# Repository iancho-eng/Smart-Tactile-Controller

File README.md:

# Smart Tactile Controller

A five-key USB-C macro pad built around an ESP32-C3 — from KiCad schematic to fabricated PCB and 3D-printed enclosure.

---

## Overview

The Smart Tactile Controller is a compact 5-key macro pad powered by an **ESP32-C3-MINI-1** module, giving it onboard Wi-Fi and BLE for wireless macro/HID use in addition to wired USB-C. The full design — schematic, PCB layout, and enclosure — was taken from concept to a fabricated, assembled board.

## Key Specifications

| Property         | Value                                              |
| ----------------- | --------------------------------------------------- |
| MCU               | ESP32-C3-MINI-1 (RISC-V, Wi-Fi + BLE)               |
| Power             | USB-C input via AP2112K-3.3 LDO regulator            |
| Input             | 5 × Cherry MX–compatible mechanical switches         |
| PCB               | 2-layer, 58 × 85 mm, 0402/0603 SMD components        |
| Enclosure         | 3D-printed, custom-designed                          |
| Cost              | ~$5 per board (PCBWay)                               |

## Hardware Files

| File                                             | Description                                    |
| -------------------------------------------------- | ------------------------------------------------- |
| [`hardware/Smart_Tactile_Controller.kicad_sch`](hardware/Smart_Tactile_Controller.kicad_sch) | Full schematic (ESP32-C3, LDO regulator, USB-C, switch matrix) |
| [`hardware/Smart_Tactile_Controller.kicad_pcb`](hardware/Smart_Tactile_Controller.kicad_pcb) | Routed 2-layer PCB layout                        |
| [`hardware/Smart_Tactile_Controller_Print.stl`](hardware/Smart_Tactile_Controller_Print.stl) | 3D-printable enclosure                           |

Open the `.kicad_sch` / `.kicad_pcb` files in **KiCad 10** to view or edit the design. The `.stl` can be sliced directly for 3D printing.

## GitHub Pages Deployment

This repo can be hosted as a static project site via GitHub Pages:

1. Push to the `main` branch.
2. In the repo settings, go to **Pages** and set the source to `main` / root (or `/docs` if you move `index.html` there).
3. The site will be published at `https://iancho-eng.github.io/Smart-Tactile-Controller/`.

### Local Preview

To preview the site locally before pushing:

```bash
python3 -m http.server 8000
```

Then open `http://localhost:8000` in your browser.

## License

Consider adding a [CERN-OHL](https://cern-ohl.web.cern.ch/) or MIT license to make the hardware design freely reusable by others.

## Status

- [x] Schematic designed in KiCad
- [x] PCB routed (2-layer)
- [x] Enclosure designed and 3D printed
- [x] Board fabricated and assembled
- [ ] Firmware / HID mapping documented

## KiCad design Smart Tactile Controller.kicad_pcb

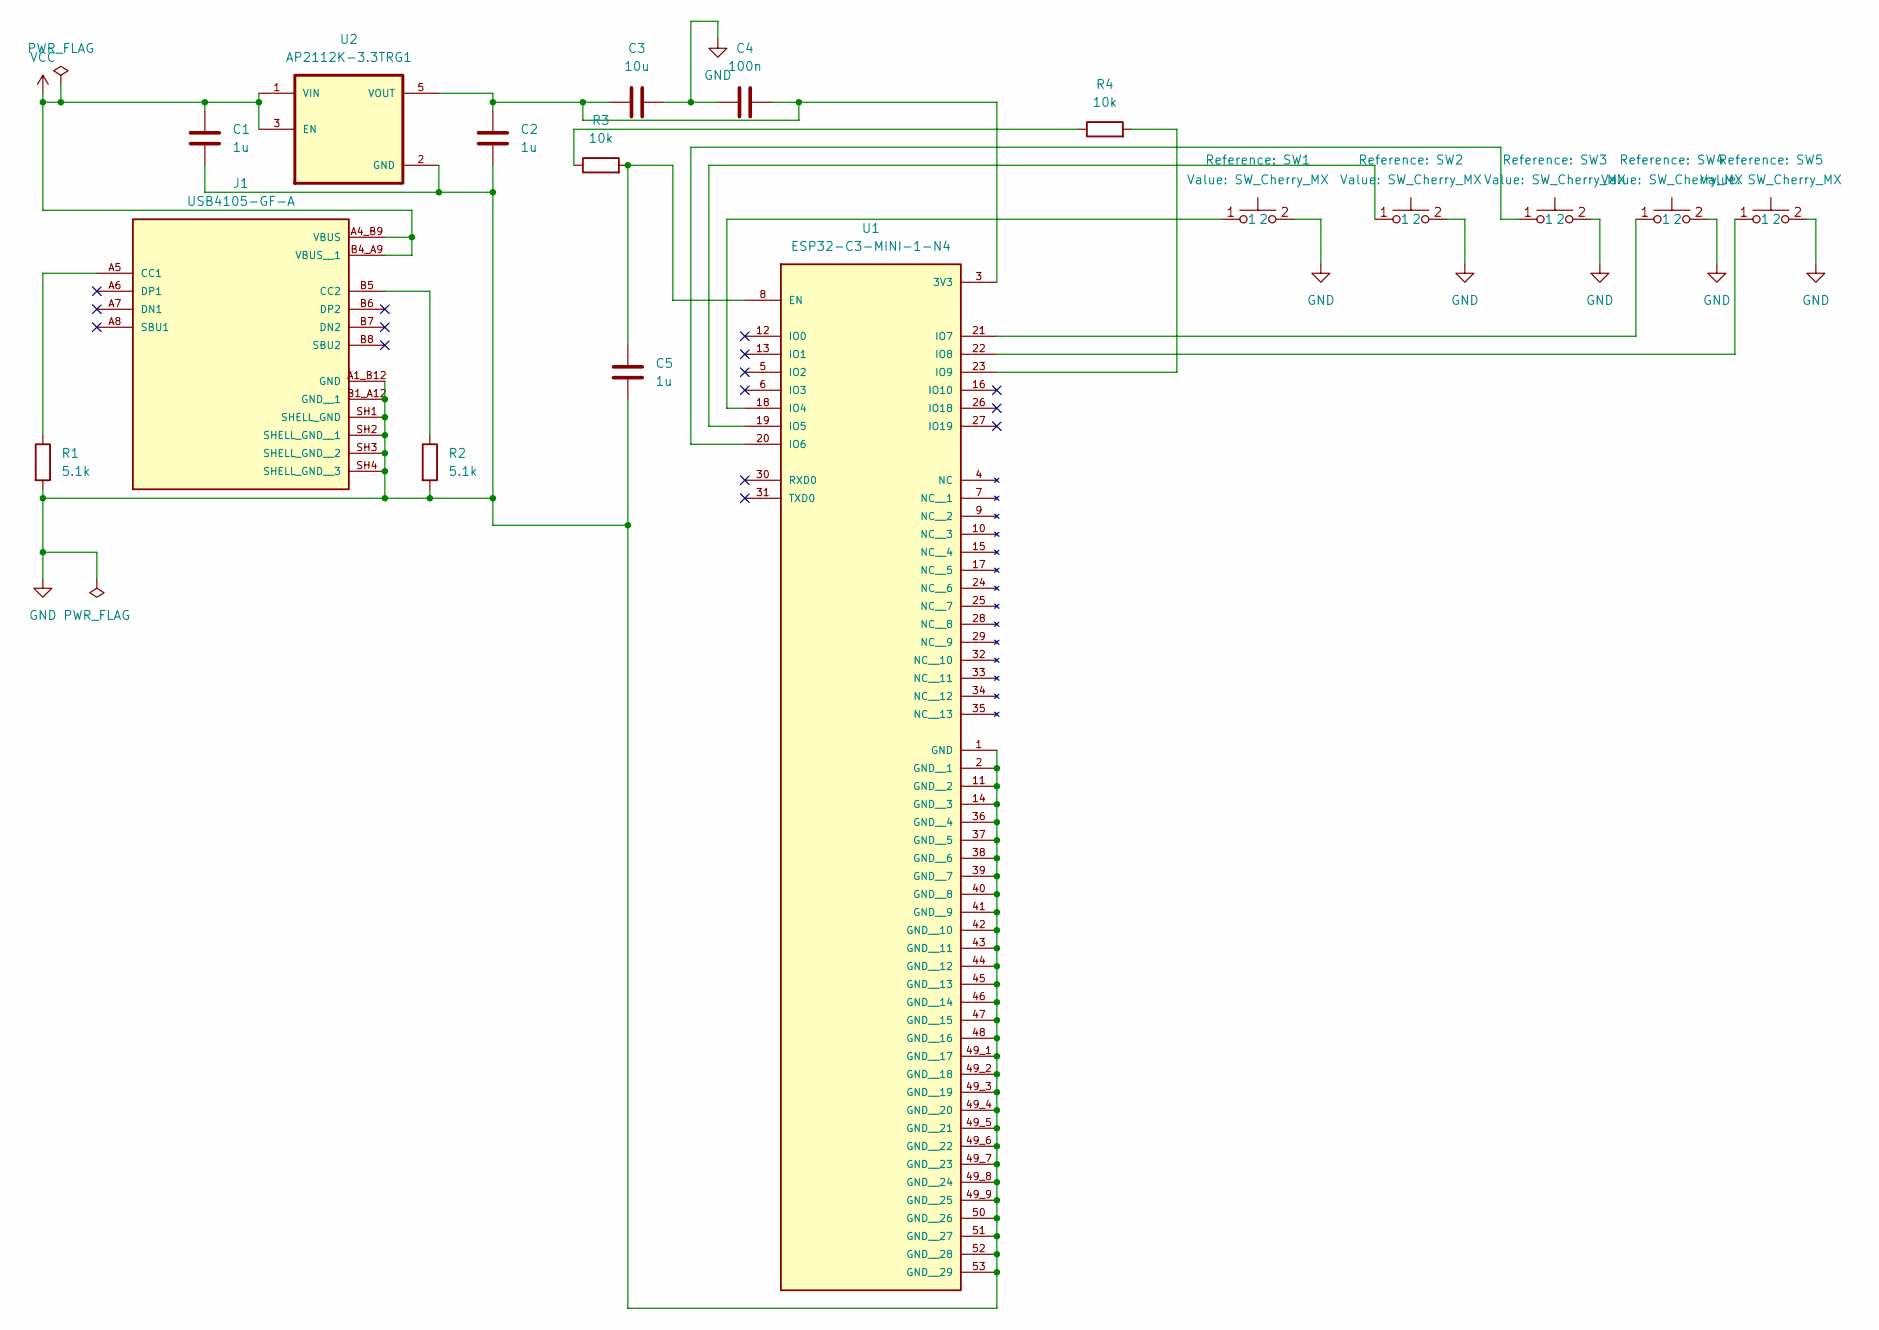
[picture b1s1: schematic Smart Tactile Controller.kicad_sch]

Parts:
C1, C2, C5: 1u; C_0402_1005Metric
C3: 10u; C_0603_1608Metric
C4: 100n; C_0402_1005Metric
J1: USB4105-GF-A; GCT_USB4105-GF-A; PARTREV B4
R1, R2: 5.1k; R_0402_1005Metric
R3, R4: 10k; R_0402_1005Metric
SW1, SW2, SW3, SW4, SW5: SW_Cherry_MX; SW_Cherry_MX_1.00u_PCB
U1: ESP32-C3-MINI-1-N4; PARTREV v1.0
U2: AP2112K-3.3TRG1; SOT95P285X140-5N; PARTREV 2-2

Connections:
GND: C1.2, C2.2, C3.2, C4.1, C5.1, J1.A1_B12 (GND), J1.B1_A12 (GND__1), J1.SH1 (SHELL_GND), J1.SH2 (SHELL_GND__1), J1.SH3 (SHELL_GND__2), J1.SH4 (SHELL_GND__3), R1.2, R2.2, SW1.2, SW2.2, SW3.2, SW4.2, SW5.2, U1.1 (GND), U1.2 (GND__1), U1.11 (GND__2), U1.14 (GND__3), U1.36 (GND__4), U1.37 (GND__5), U1.38 (GND__6), U1.39 (GND__7), U1.40 (GND__8), U1.41 (GND__9), U1.42 (GND__10), U1.43 (GND__11), U1.44 (GND__12), U1.45 (GND__13), U1.46 (GND__14), U1.47 (GND__15), U1.48 (GND__16), U1.49_1 (GND__17), U1.49_2 (GND__18), U1.49_3 (GND__19), U1.49_4 (GND__20), U1.49_5 (GND__21), U1.49_6 (GND__22), U1.49_7 (GND__23), U1.49_8 (GND__24), U1.49_9 (GND__25), U1.50 (GND__26), U1.51 (GND__27), U1.52 (GND__28), U1.53 (GND__29), U2.2 (GND)
unnamed: J1.A5 (CC1), R1.1
unnamed: J1.B5 (CC2), R2.1
unnamed: R3.1, R4.1
unnamed: C2.1, C3.1, C4.2, U1.3 (3V3), U2.5 (VOUT)
unnamed: C5.2, R3.2, U1.8 (EN)
unnamed: SW1.1, U1.18 (IO4)
unnamed: SW2.1, U1.19 (IO5)
unnamed: SW3.1, U1.20 (IO6)
unnamed: SW4.1, U1.21 (IO7)
unnamed: SW5.1, U1.22 (IO8)
unnamed: R4.2, U1.23 (IO9)
VCC: C1.1, J1.A4_B9 (VBUS), J1.B4_A9 (VBUS__1), U2.1 (VIN), U2.3 (EN)

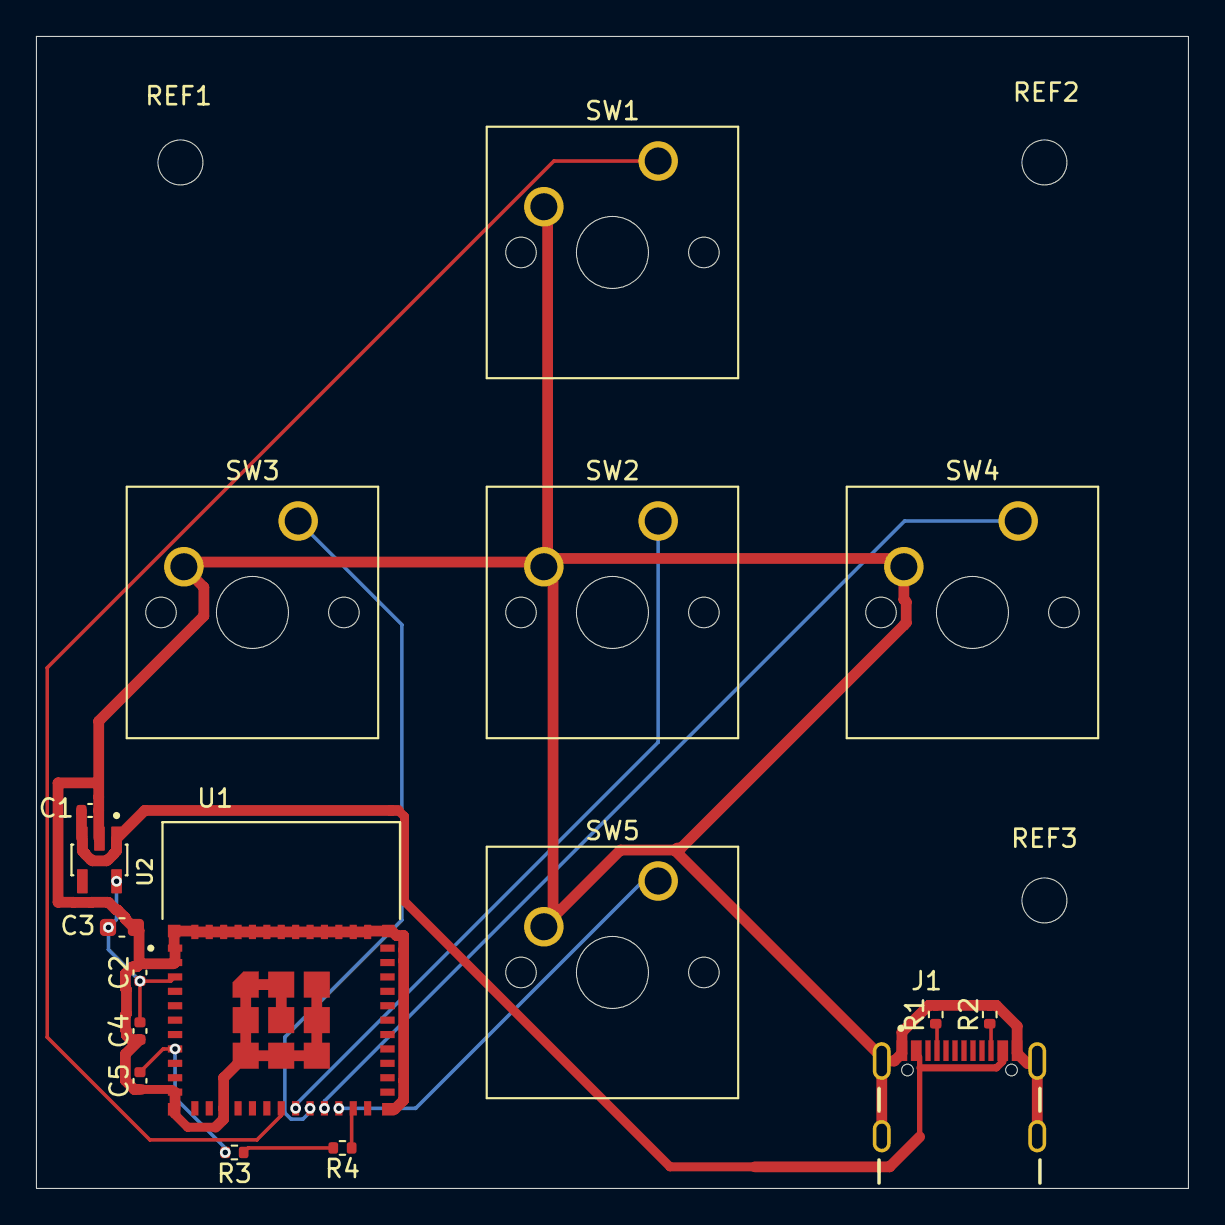
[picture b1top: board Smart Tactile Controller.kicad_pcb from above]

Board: 2 copper layers, 64.0 x 64.0 mm, 20 parts (0 on the bottom side), 13 nets.

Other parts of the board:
REF1, REF2, REF3: MountingHole_2.5mm
